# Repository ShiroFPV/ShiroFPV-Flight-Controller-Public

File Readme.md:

## 📖 Credits 
This project was heavily inspired by the amazing work of AcciFPV. Their creativity and open sharing within the FPV community motivated me to start developing my own hardware. While this design is fully original, AcciFPV’s approach and passion for innovation definitely sparked many of the ideas behind it. Huge thanks to them for contributing so much to the FPV scene — check out their projects for more awesome stuff!
[Github](https://gist.github.com/jesuslg123)
[AcciFPV Flight Controller](https://oshwlab.com/jesuslg123/f4-v1)

## 📖 Documentation

This repository includes a full website with detailed documentation. You can view the live documentation here:

[Website](https://shirofpv.github.io/ShiroFPV-Flight-Controller-Public/Website/index.html)

The documentation covers:
* **Hardware Specifications:** A breakdown of components.
* **Software & Firmware:** Information on compatible firmware (Betaflight) and how to get the latest builds.
* **Setup Guide:** A step-by-step guide to flashing firmware, and getting your drone in the air.

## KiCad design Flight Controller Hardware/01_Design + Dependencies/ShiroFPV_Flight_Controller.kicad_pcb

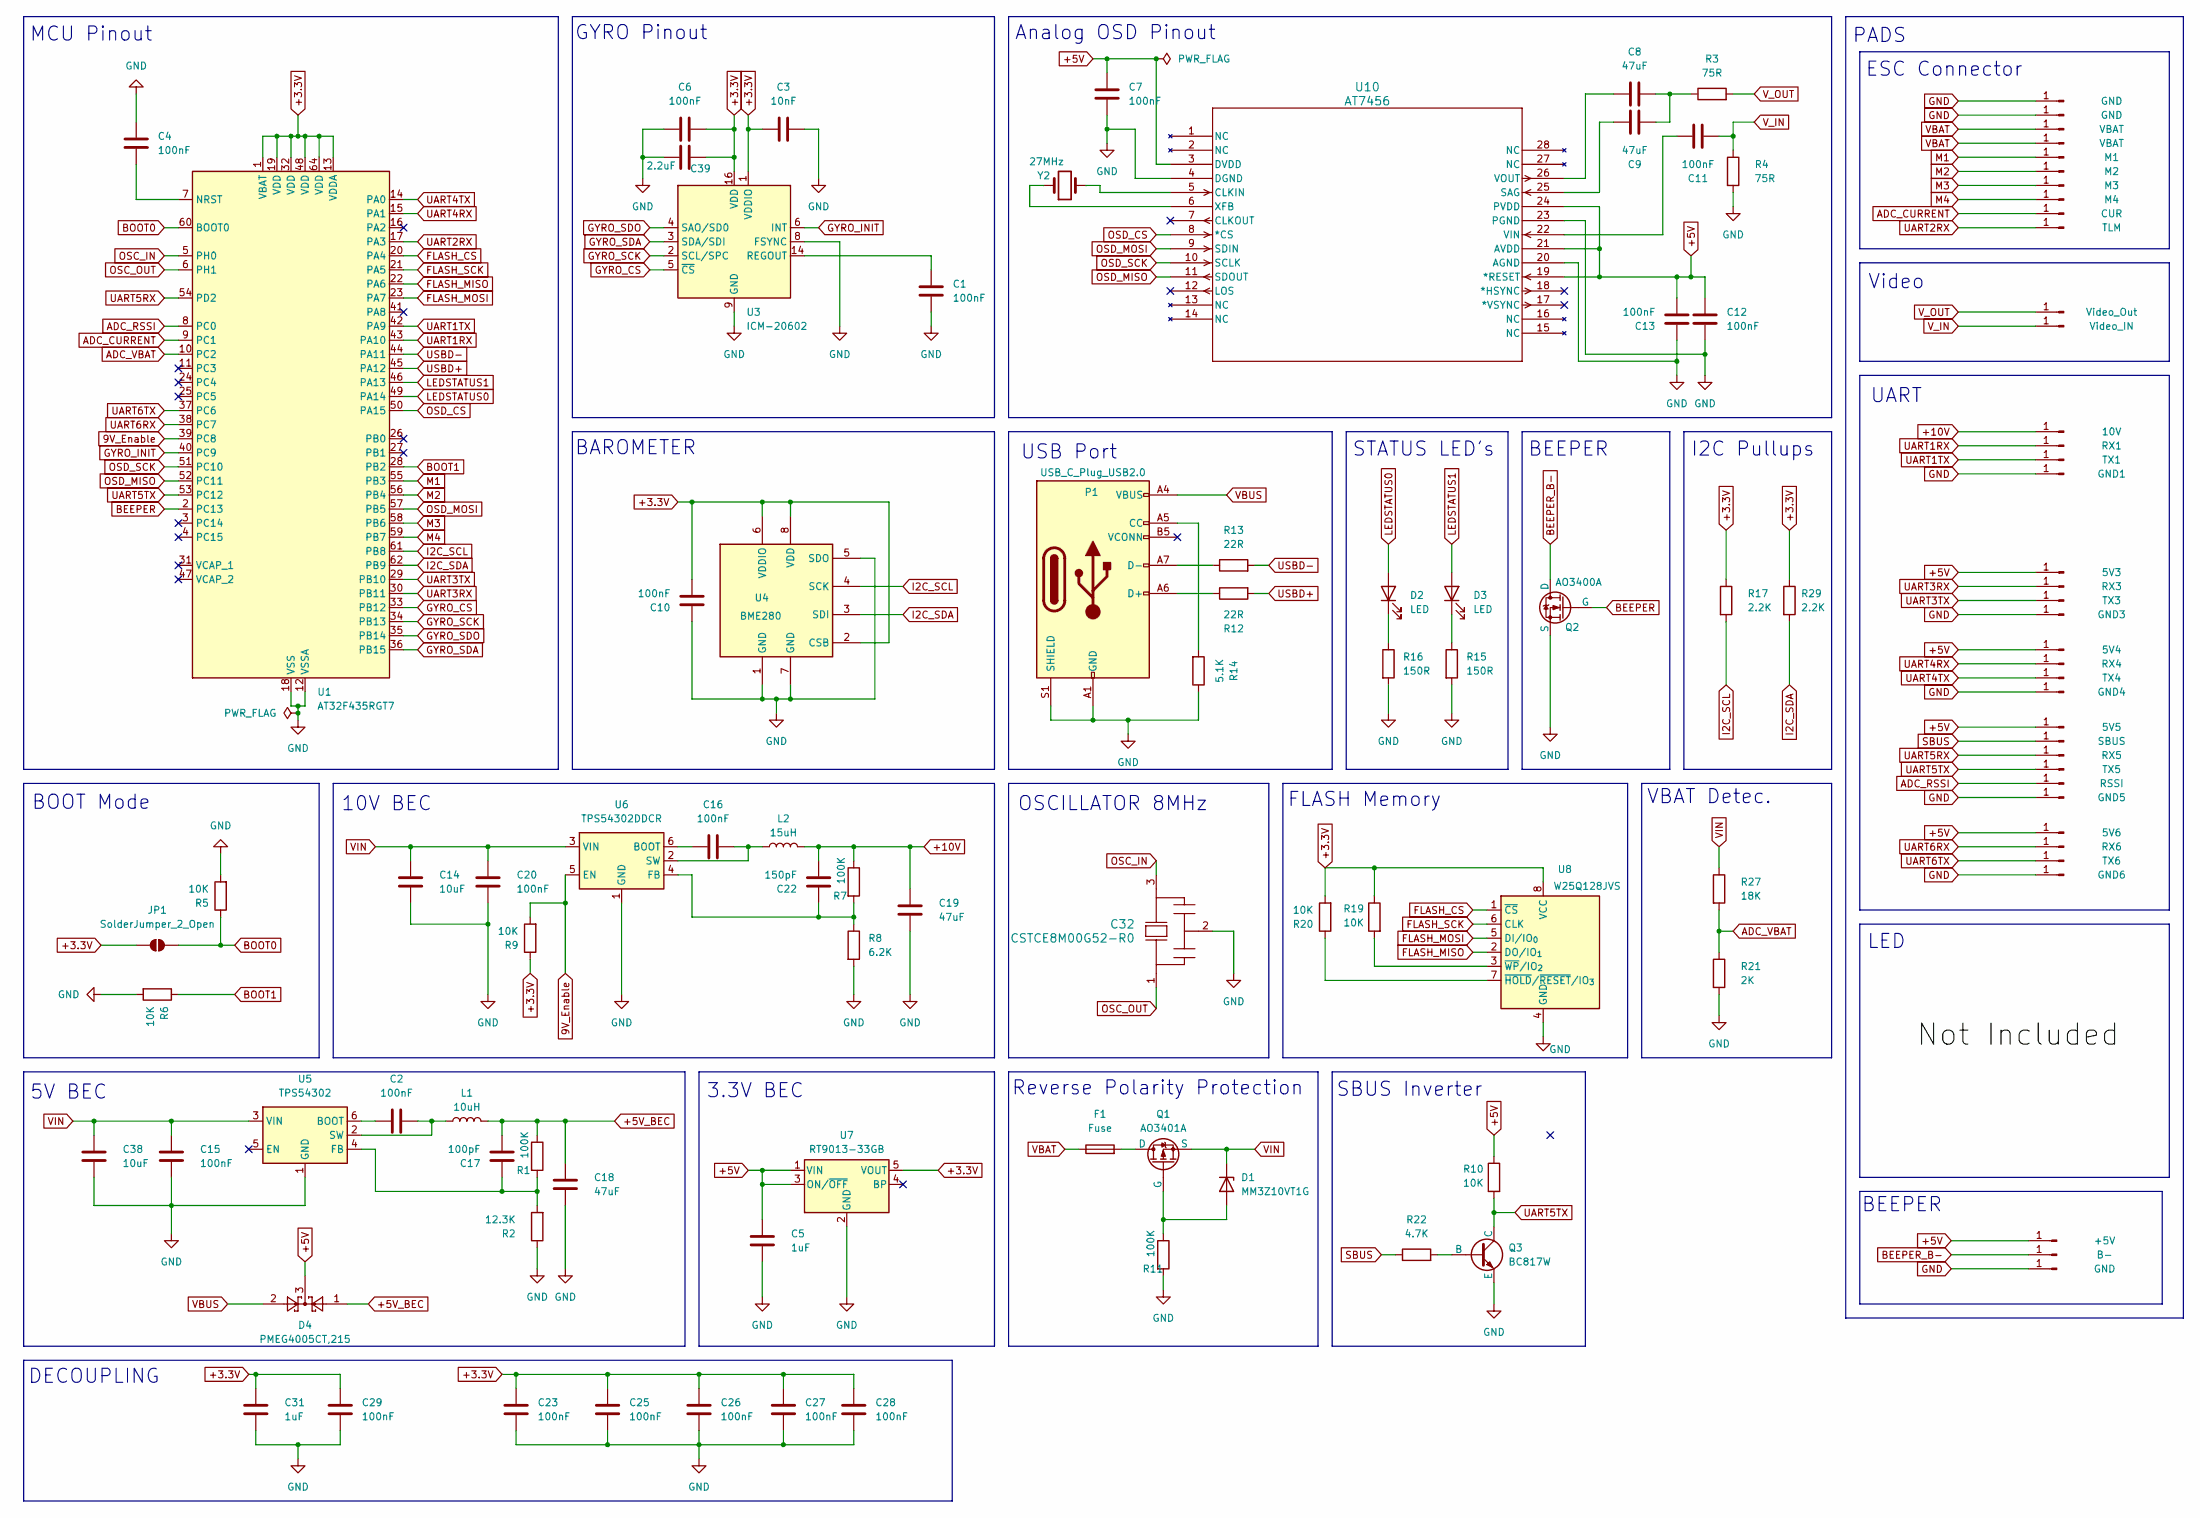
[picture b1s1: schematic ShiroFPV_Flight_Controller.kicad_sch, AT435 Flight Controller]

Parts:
C1, C2, C4, C6, C7, C10, C11, C12, C13, C15, C16, C20, C23, C25, C26, C27, C28, C29: 100nF; C_0603_1608Metric; MPN CC0603JRX7R8BB104
C3: 10nF; C_0603_1608Metric; MPN C0603C103F3GECAUTO
C5, C31: 1uF; C_0603_1608Metric; MPN 1uF_0603_X7R_16V
C8, C9: 47uF; C_0603_1608Metric; MPN GRM31CR61E476ME44L
C14, C38: 10uF; C_1206_3216Metric; MPN CL31B106KBHNNNE
C17: 100pF; C_0603_1608Metric; MPN CC0603JRX7R9BB101
C18, C19: 47uF; C_1206_3216Metric; MPN GRM31CR61E476ME44L
C22: 150pF; C_0603_1608Metric; MPN CC0603JRX7R9BB151
C32: CSTCE8M00G52-R0; 8MHz-Osciallator.kicad_sym; MPN CSTNE8M00G520000R0
C39: 2.2uF; C_0603_1608Metric; MPN CC0603KRX5R6BB225
D1: MM3Z10VT1G; D_SOD-323_HandSoldering; MPN LM3Z10VT1G
D2, D3: LED; LED_0603_1608Metric
D4: PMEG4005CT,215; SOT-23
F1: Fuse; Fuse_1206_3216Metric
J1, J2, J46: GND; TestPoint_Pad_1.0x1.0mm
J3, J4: VBAT; TestPoint_Pad_1.0x1.0mm
J5: M1; TestPoint_Pad_1.0x1.0mm
J6: M2; TestPoint_Pad_1.0x1.0mm
J7: M3; TestPoint_Pad_1.0x1.0mm
J8: M4; TestPoint_Pad_1.0x1.0mm
J9: CUR; TestPoint_Pad_1.0x1.0mm
J10: TLM; TestPoint_Pad_1.0x1.0mm
J11: Video_Out; TestPoint_Pad_1.0x1.0mm
J12: Video_IN; TestPoint_Pad_1.0x1.0mm
J13: 5V3; TestPoint_Pad_1.0x1.0mm
J14: RX3; TestPoint_Pad_1.0x1.0mm
J15: TX3; TestPoint_Pad_1.0x1.0mm
J16: GND3; TestPoint_Pad_1.0x1.0mm
J17: 5V4; TestPoint_Pad_1.0x1.0mm
J18: RX4; TestPoint_Pad_1.0x1.0mm
J19: TX4; TestPoint_Pad_1.0x1.0mm
J20: GND4; TestPoint_Pad_1.0x1.0mm
J24: +5V; TestPoint_Pad_1.0x1.0mm
J25: RSSI; TestPoint_Pad_1.0x1.0mm
J26: GND5; TestPoint_Pad_1.0x1.0mm
J29: SBUS; TestPoint_Pad_1.0x1.0mm
J30: 5V5; TestPoint_Pad_1.0x1.0mm
J31: RX5; TestPoint_Pad_1.0x1.0mm
J32: TX5; TestPoint_Pad_1.0x1.0mm
J33: RX6; TestPoint_Pad_1.0x1.0mm
J34: 5V6; TestPoint_Pad_1.0x1.0mm
J35: GND6; TestPoint_Pad_1.0x1.0mm
J36: TX6; TestPoint_Pad_1.0x1.0mm
J37: 10V; TestPoint_Pad_1.0x1.0mm
J38: RX1; TestPoint_Pad_1.0x1.0mm
J39: TX1; TestPoint_Pad_1.0x1.0mm
J40: GND1; TestPoint_Pad_1.0x1.0mm
J42: B-; TestPoint_Pad_1.0x1.0mm
JP1: SolderJumper_2_Open; SolderJumper-2_P1.3mm_Open_Pad1.0x1.5mm
L1: 10uH; L_APV_APH0412
L2: 15uH; L_APV_APH0412; MPN YSPI0530-150M
P1: USB_C_Plug_USB2.0; USB_C_Receptacle_G-Switch_GT-USB-7010ASV; MPN GT-USB-7010ASV
Q1: AO3401A; SOT-23
Q2: AO3400A; SOT-23
Q3: BC817W; SOT-323_SC-70
R1, R7, R11: 100K; R_0603_1608Metric; MPN RC0603FR-07100KL
R2: 12.3K; R_0603_1608Metric; MPN RC0603FR-0712K3L
R3, R4: 75R; R_0603_1608Metric; MPN RC0603FR-0775RL
R5, R6, R9, R10, R19, R20: 10K; R_0603_1608Metric; MPN RC0603FR-0710KL
R8: 6.2K; R_0603_1608Metric; MPN RC0603FR-076K2L
R12, R13: 22R; R_0603_1608Metric; MPN RC0603FR-0722RL
R14: 5.1K; R_0603_1608Metric; MPN RC0603FR-075K1L
R15, R16: 150R; R_0603_1608Metric; MPN RC0603FR-07150RL
R17, R29: 2.2K; R_0603_1608Metric; MPN RC0603FR-072K2L
R21: 2K; R_0603_1608Metric; MPN RC0603FR-072KL
R22: 4.7K; R_0603_1608Metric; MPN RC0603FR-074K7L
R27: 18K; R_0603_1608Metric; MPN RC0603FR-0718KL
U1: AT32F435RGT7; LQFP-64_10x10mm_P0.5mm
U3: ICM-20602; LGA-16_3x3mm_P0.5mm_LayoutBorder3x5y; MPN ICM-20602
U4: BME280; Bosch_LGA-8_2.5x2.5mm_P0.65mm_ClockwisePinNumbering; MPN BME280
U5: TPS54302; SOT-23-6; MPN TPS54302DDCR
U6: TPS54302DDCR; SOT-23-6; MPN TPS54302DDCR
U7: RT9013-33GB; SOT-23-5; MPN RT9013-33GB
U8: W25Q128JVS; SOIC-8_5.3x5.3mm_P1.27mm; MPN W25Q128JVSIQ
U10: AT7456; MPN AT7456E
Y2: 27MHz; Crystal_SMD_3225-4Pin_3.2x2.5mm

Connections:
9V_Enable: R9.2, U1.39 (PC8), U6.5 (EN)
+3.3V: C3.1, C6.2, C10.1, C23.1, C25.1, C26.1, C27.1, C28.1, C29.1, C31.1, C39.1, JP1.1 (A), R9.1, R17.1, R19.1, R20.2, R29.1, U1.1 (VBAT), U1.13 (VDDA), U1.19 (VDD), U1.32 (VDD), U1.48 (VDD), U1.64 (VDD), U3.1 (VDDIO), U3.16 (VDD), U4.2 (CSB), U4.6 (VDDIO), U4.8 (VDD), U7.5 (VOUT), U8.8 (VCC)
+5V: C5.1, C7.2, C12.2, C13.1, D4.3, J13.1, J17.1, J24.1, J30.1, J34.1, R10.1, U7.1 (VIN), U7.3 (ON/~OFF), U10.3 (DVDD), U10.19 (*RESET), U10.21 (AVDD), U10.24 (PVDD)
+5V_BEC: C17.1, C18.1, D4.1, L1.2, R1.1
+10V: C19.1, C22.1, J37.1, L2.2, R7.1
ADC_CURRENT: J9.1, U1.9 (PC1)
ADC_RSSI: J25.1, U1.8 (PC0)
ADC_VBAT: R21.1, R27.2, U1.10 (PC2)
BEEPER: Q2.2 (G), U1.2 (PC13)
BEEPER_B-: J42.1, Q2.1 (D)
BOOT0: JP1.2 (B), R5.1, U1.60 (BOOT0)
BOOT1: R6.1, U1.28 (PB2)
FLASH_CS: U1.20 (PA4), U8.1 (~CS)
FLASH_MISO: U1.22 (PA6), U8.2 (DO/IO_{1})
FLASH_MOSI: U1.23 (PA7), U8.5 (DI/IO_{0})
FLASH_SCK: U1.21 (PA5), U8.6 (CLK)
GND: C1.1, C3.2, C4.1, C5.2, C6.1, C7.1, C10.2, C12.1, C13.2, C14.2, C15.2, C18.2, C19.2, C20.2, C23.2, C25.2, C26.2, C27.2, C28.2, C29.2, C31.2, C32.2, C38.2, C39.2, J1.1, J2.1, J16.1, J20.1, J26.1, J35.1, J40.1, J46.1, P1.A1 (GND), P1.A12 (GND), P1.B1 (GND), P1.B12 (GND), P1.S1 (SHIELD), Q2.3 (S), Q3.3 (E), R2.1, R4.2, R5.2, R6.2, R8.2, R11.2, R14.1, R15.2, R16.2, R21.2, U1.12 (VSSA), U1.18 (VSS), U1.63 (VSS), U3.8 (FSYNC), U3.9 (GND), U3.10 (GND), U3.11 (GND), U3.12 (GND), U3.13 (GND), U3.15 (GND), U4.1 (GND), U4.5 (SDO), U4.7 (GND), U5.1 (GND), U6.1 (GND), U7.2 (GND), U8.4 (GND), U10.4 (DGND), U10.20 (AGND), U10.23 (PGND), Y2.3, Y2.4
GYRO_CS: U1.33 (PB12), U3.5 (~CS)
GYRO_INIT: U1.40 (PC9), U3.6 (INT)
GYRO_SCK: U1.34 (PB13), U3.2 (SCL/SPC)
GYRO_SDA: U1.36 (PB15), U3.3 (SDA/SDI)
GYRO_SDO: U1.35 (PB14), U3.4 (SAO/SD0)
I2C_SCL: R17.2, U1.61 (PB8), U4.4 (SCK)
I2C_SDA: R29.2, U1.62 (PB9), U4.3 (SDI)
LEDSTATUS0: D2.2 (A), U1.49 (PA14)
LEDSTATUS1: D3.2 (A), U1.46 (PA13)
M1: J5.1, U1.55 (PB3)
M2: J6.1, U1.56 (PB4)
M3: J7.1, U1.58 (PB6)
M4: J8.1, U1.59 (PB7)
unnamed: C8.2, C9.2, R3.1
unnamed: D1.2 (A), Q1.2 (G), R11.1
unnamed: D2.1 (K), R16.1
unnamed: D3.1 (K), R15.1
unnamed: P1.A5 (CC), R14.2
unnamed: P1.A6 (D+), R12.1
unnamed: P1.A7 (D-), R13.1
unnamed: F1.2, Q1.1 (D)
unnamed: Q3.2 (B), R22.2
unnamed: C4.2, U1.7 (NRST)
unnamed: C1.2, U3.14 (REGOUT)
unnamed: C2.2, U5.6 (BOOT)
unnamed: C17.2, R1.2, R2.2, U5.4 (FB)
unnamed: C2.1, L1.1, U5.2 (SW)
unnamed: C16.2, U6.6 (BOOT)
unnamed: C22.2, R7.2, R8.1, U6.4 (FB)
unnamed: C16.1, L2.1, U6.2 (SW)
unnamed: R20.1, U8.7 (~HOLD/~RESET/IO_{3})
unnamed: R19.2, U8.3 (~WP/IO_{2})
unnamed: U10.5 (CLKIN), Y2.2
unnamed: C9.1, U10.25 (SAG)
unnamed: C11.1, U10.22 (VIN)
unnamed: C8.1, U10.26 (VOUT)
unnamed: U10.6 (XFB), Y2.1
OSC_IN: C32.3, U1.5 (PH0)
OSC_OUT: C32.1, U1.6 (PH1)
OSD_CS: U1.50 (PA15), U10.8 (*CS)
OSD_MISO: U1.52 (PC11), U10.11 (SDOUT)
OSD_MOSI: U1.57 (PB5), U10.9 (SDIN)
OSD_SCK: U1.51 (PC10), U10.10 (SCLK)
SBUS: J29.1, R22.1
UART1RX: J38.1, U1.43 (PA10)
UART1TX: J39.1, U1.42 (PA9)
UART2RX: J10.1, U1.17 (PA3)
UART3RX: J14.1, U1.30 (PB11)
UART3TX: J15.1, U1.29 (PB10)
UART4RX: J18.1, U1.15 (PA1)
UART4TX: J19.1, U1.14 (PA0)
UART5RX: J31.1, U1.54 (PD2)
UART5TX: J32.1, Q3.1 (C), R10.2, U1.53 (PC12)
UART6RX: J33.1, U1.38 (PC7)
UART6TX: J36.1, U1.37 (PC6)
USBD+: R12.2, U1.45 (PA12)
USBD-: R13.2, U1.44 (PA11)
VBAT: F1.1, J3.1, J4.1
VBUS: D4.2, P1.A4 (VBUS), P1.A9 (VBUS), P1.B4 (VBUS), P1.B9 (VBUS)
VIN: C14.1, C15.1, C20.1, C38.1, D1.1 (K), Q1.3 (S), R27.1, U5.3 (VIN), U6.3 (VIN)
V_IN: C11.2, J12.1, R4.1
V_OUT: J11.1, R3.2

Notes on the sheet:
DECOUPLING
ESC Connector
OSCILLATOR 8MHz
LED
5V BEC
VBAT Detec.
UART
FLASH Memory
PADS
BAROMETER
BEEPER
Video
STATUS LED's
I2C Pullups
BEEPER
BOOT Mode
MCU Pinout
Analog OSD Pinout
10V BEC
GYRO Pinout
3.3V BEC
USB Port
Reverse Polarity Protection
SBUS Inverter

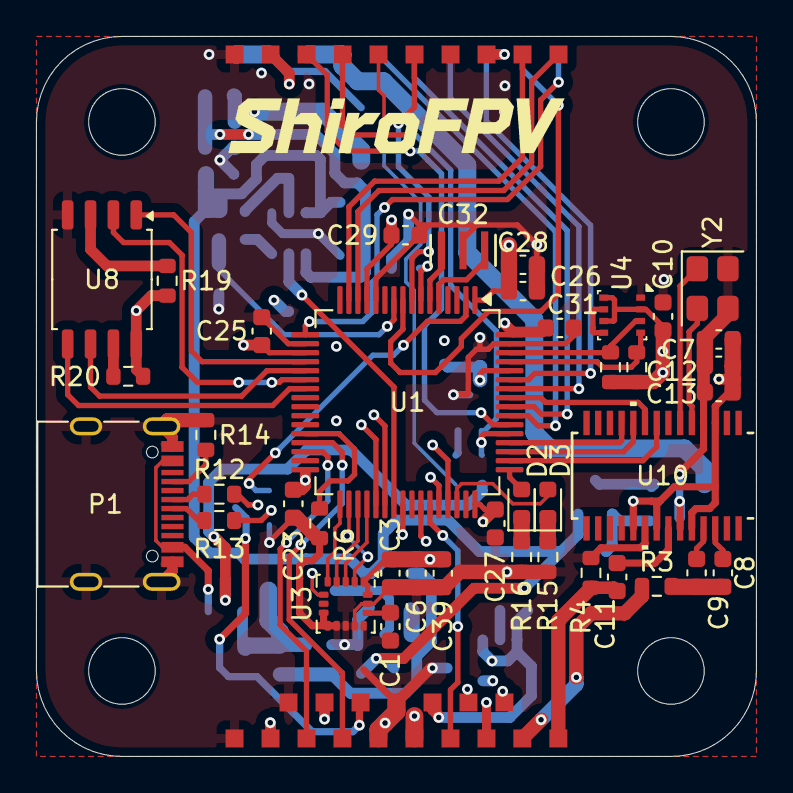
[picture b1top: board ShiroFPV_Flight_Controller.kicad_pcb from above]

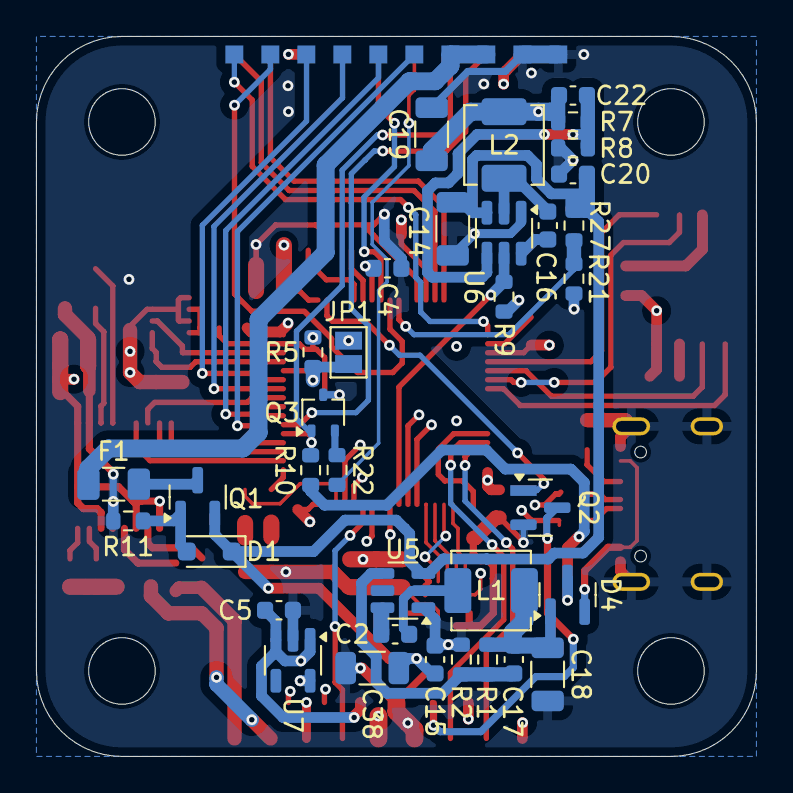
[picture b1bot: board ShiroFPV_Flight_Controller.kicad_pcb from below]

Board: 4 copper layers, 40.0 x 40.0 mm, 112 parts (45 on the bottom side), 79 nets.

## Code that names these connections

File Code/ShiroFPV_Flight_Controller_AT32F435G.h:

#pragma once

#define TARGET_BOARD_IDENTIFIER "ShiroFPV_AT32F435G" // Shiro AT435
#define FC_TARGET_MCU AT32F435G

#define BOARD_NAME "ShiroFPV_AT435G"
#define MANUFACTURER_ID CUSTOM

// Features
#define USE_ACC
#define USE_GYRO
#define USE_BARO
#define USE_FLASH
#define USE_MAX7456
#define USE_ADC

// Sensors
#define USE_GYRO_SPI_ICM20602
#define USE_ACC_SPI_ICM20602
#define USE_BARO_BME280
#define USE_FLASH_W25Q128FV

// IO
#define LED0_PIN PA14
#define LED1_PIN PA13
#define BEEPER_PIN PC13
#define BEEPER_INVERTED

// SPI Gyro SPI4
#define USE_SPI_GYRO
#define GYRO_1_EXTI_PIN PC9
#define GYRO_1_CS_PIN PB12
#define GYRO_1_SPI_INSTANCE SPI4
#define GYRO_1_ALIGN CW0_DEG
#define GYRO_1_ALIGN_YAW 1800

#define SPI1_SCK_PIN PA5
#define SPI1_SDI_PIN PA6
#define SPI1_SDO_PIN PA7

#define SPI2_SCK_PIN PB13  // Flash
#define SPI2_SDI_PIN PB14
#define SPI2_SDO_PIN PB15
#define FLASH_CS_PIN PB12
#define FLASH_SPI_INSTANCE SPI2

#define SPI3_SCK_PIN PC10  // OSD
#define SPI3_SDI_PIN PC11
#define SPI3_SDO_PIN PB5
#define MAX7456_SPI_CS_PIN PA15
#define MAX7456_SPI_INSTANCE SPI3

// ADC
#define ADC_VBAT_PIN PC1
#define ADC_RSSI_PIN PC2
#define ADC_CURR_PIN PC3
#define ADC_INSTANCE ADC3
#define ADC1_DMA_OPT 11

// UARTs (Netlist-match)
#define UART1_TX_PIN PA9  // J39
#define UART1_RX_PIN PA10 // J38
#define UART2_TX_PIN PA2
#define UART2_RX_PIN PA3
#define UART3_TX_PIN PB10 // TLM J15?
#define UART3_RX_PIN PB11 // J14
#define UART4_TX_PIN PA0
#define UART4_RX_PIN PA1
#define UART5_TX_PIN PC12
#define UART5_RX_PIN PD2
#define UART6_TX_PIN PC6
#define UART6_RX_PIN PC7

// TIMERS & MOTORS (Netlist J5-8)
#define TIMER_PIN_MAPPING \
    TIMER_PIN_MAP( 0, PB3 , 1, 0) \
    TIMER_PIN_MAP( 1, PB4 , 1, 0) \
    TIMER_PIN_MAP( 2, PB6 , 2, 0) \
    TIMER_PIN_MAP( 3, PB7 , 2, 0) \
    TIMER_PIN_MAP( 4, PC8 , 2, 0)

#define MOTOR1_PIN PB3
#define MOTOR2_PIN PB4
#define MOTOR3_PIN PB6
#define MOTOR4_PIN PB7

// I2C Baro
#define BARO_I2C_INSTANCE I2CDEV_1
#define I2C1_SCL_PIN PB8
#define I2C1_SDA_PIN PB9

// PINIO
#define PINIO1_PIN PC8
#define PINIO1_BOX 40
#define PINIO1_CONFIG 129

// Defaults
#define DEFAULT_BLACKBOX_DEVICE BLACKBOX_DEVICE_FLASH
#define DEFAULT_CURRENT_METER_SOURCE CURRENT_METER_ADC
#define DEFAULT_VOLTAGE_METER_SOURCE VOLTAGE_METER_ADC
#define DEFAULT_DSHOT_BURST DSHOT_DMAR_ON

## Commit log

2026-01-28 First Push
    Pushed the first Version of the Project
2026-01-28 Reorganize project directory structure
    Moved hardware design and website files into new 'Flight Controller Hardware' and 'Website' directories, respectively, for improved organization.
2026-01-28 Fixed Mistake
    Fixed a mistake made in the Pin Config of two Mosfets.
2026-01-29 Lots of new stuff
    Added a new Website thus it not beeing finished yet.
    and updated the PCB
2026-01-30 Update documentation and add images to website
    Revised Readme with credits and updated links, improved hardware, overview, setup, and software HTML files for clarity and accuracy, to enhance the website's visual content.
2026-01-30 Add backups; update KiCad project files
    Add three timestamped project backup ZIPs for ShiroFPV_Flight_Controller. Update .kicad_prl to set active_layer from 0 to 2. Update .kicad_sch to remove fields_autoplaced for D2 and D3 and replace th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
2026-02-02 new version
